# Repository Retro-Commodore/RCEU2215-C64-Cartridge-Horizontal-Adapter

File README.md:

# RCEU2215 - C64 Cartridge Horizontal Adapter
Cartridge vertical to horizontal adapter, i.e. for C128DCR and 1541 Ultimate

This is an adapter I created for my Commodore 128 DCR and 1541 Ultimate 2(+).
I got annoyed that the C128 would reset by cables and the back wall, on the reset switch of any cart with a reset button, due to it's limited space up against the back wall. 
Also the IEC cable connectors would cross tightly and strain the connectors on both IEC and U2 ports. 
The U2+ IEC got moved back in this new design, but not enough, and now the tape connector + audio connectors are in the way.

The result was to make this adapter, and the items below fixes that problem

* 2 (nylon) standoffs 
* 44pin Edge connector 2.54mm pitch, straight

Standoffs and connector can be found on ebay, or perhaps your favorite local store.

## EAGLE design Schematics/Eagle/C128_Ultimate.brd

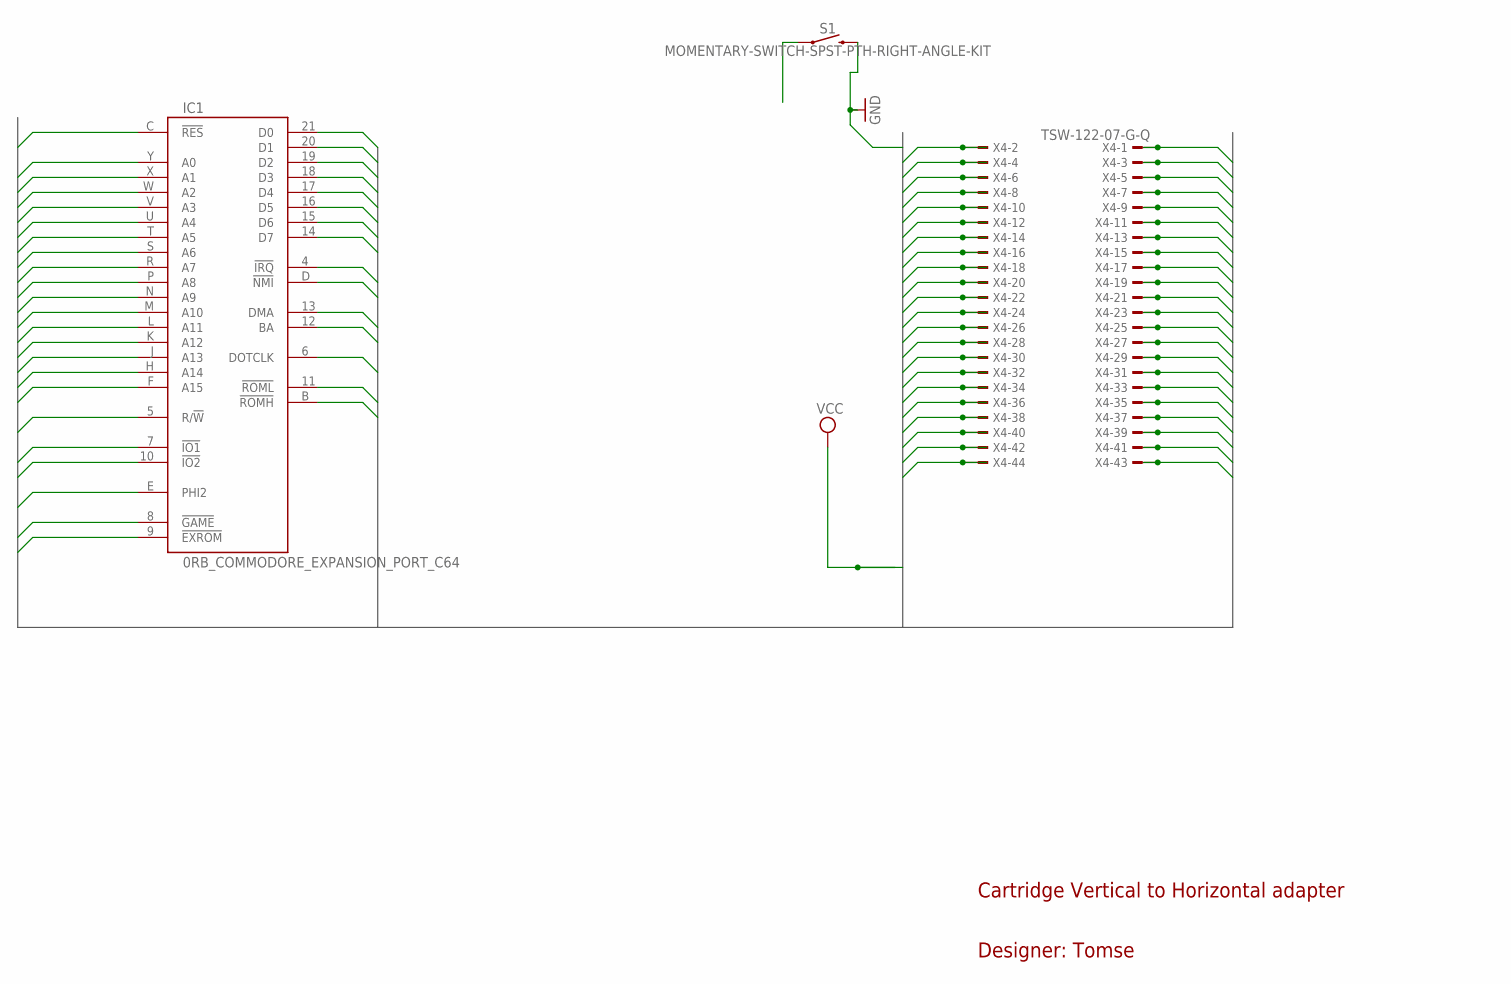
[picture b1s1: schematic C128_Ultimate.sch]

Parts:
IC1: 0RB_COMMODORE_EXPANSION_PORT_C64; 0RB_COMMODORE_MA100-22-2
S1: MOMENTARY-SWITCH-SPST-PTH-RIGHT-ANGLE-KIT; TACTILE_SWITCH_PTH_RIGHT_ANGLE_KIT
X4: TSW-122-07-G-Q; TSW-122-XX-G-Q

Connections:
!DMA: IC1.13 (DMA), X4.26
!EXROM: IC1.9 (!EXROM), X4.18
!GAME: IC1.8 (!GAME), X4.16
!IO1: IC1.7 (!IO1), X4.14
!IO2: IC1.10 (!IO2), X4.20
!IRQ: IC1.4 (!IRQ), X4.8
!NMI: IC1.D (!NMI), X4.7
!RES: IC1.C (!RES), S1.1, X4.5
!ROMH: IC1.B (!ROMH), X4.3
!ROML: IC1.11 (!ROML), X4.22
A0: IC1.Y (A0), X4.41
A1: IC1.X (A1), X4.39
A2: IC1.W (A2), X4.37
A3: IC1.V (A3), X4.35
A4: IC1.U (A4), X4.33
A5: IC1.T (A5), X4.31
A6: IC1.S (A6), X4.29
A7: IC1.R (A7), X4.27
A8: IC1.P (A8), X4.25
A9: IC1.N (A9), X4.23
A10: IC1.M (A10), X4.21
A11: IC1.L (A11), X4.19
A12: IC1.K (A12), X4.17
A13: IC1.J (A13), X4.15
A14: IC1.H (A14), X4.13
A15: IC1.F (A15), X4.11
BA: IC1.12 (BA), X4.24
D0: IC1.21 (D0), X4.42
D1: IC1.20 (D1), X4.40
D2: IC1.19 (D2), X4.38
D3: IC1.18 (D3), X4.36
D4: IC1.17 (D4), X4.34
D5: IC1.16 (D5), X4.32
D6: IC1.15 (D6), X4.30
D7: IC1.14 (D7), X4.28
DOTCLK: IC1.6 (DOTCLK), X4.12
GND: IC1.1 (GND), IC1.22 (GND), IC1.A (GND), IC1.Z (GND), S1.2, X4.1, X4.2, X4.43, X4.44
PHI2: IC1.E (PHI2), X4.9
R!W: IC1.5 (R/!W), X4.10
VCC: IC1.2 (VCC), IC1.3 (VCC), X4.4, X4.6

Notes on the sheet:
Cartridge Vertical to Horizontal adapter
Designer: Tomse

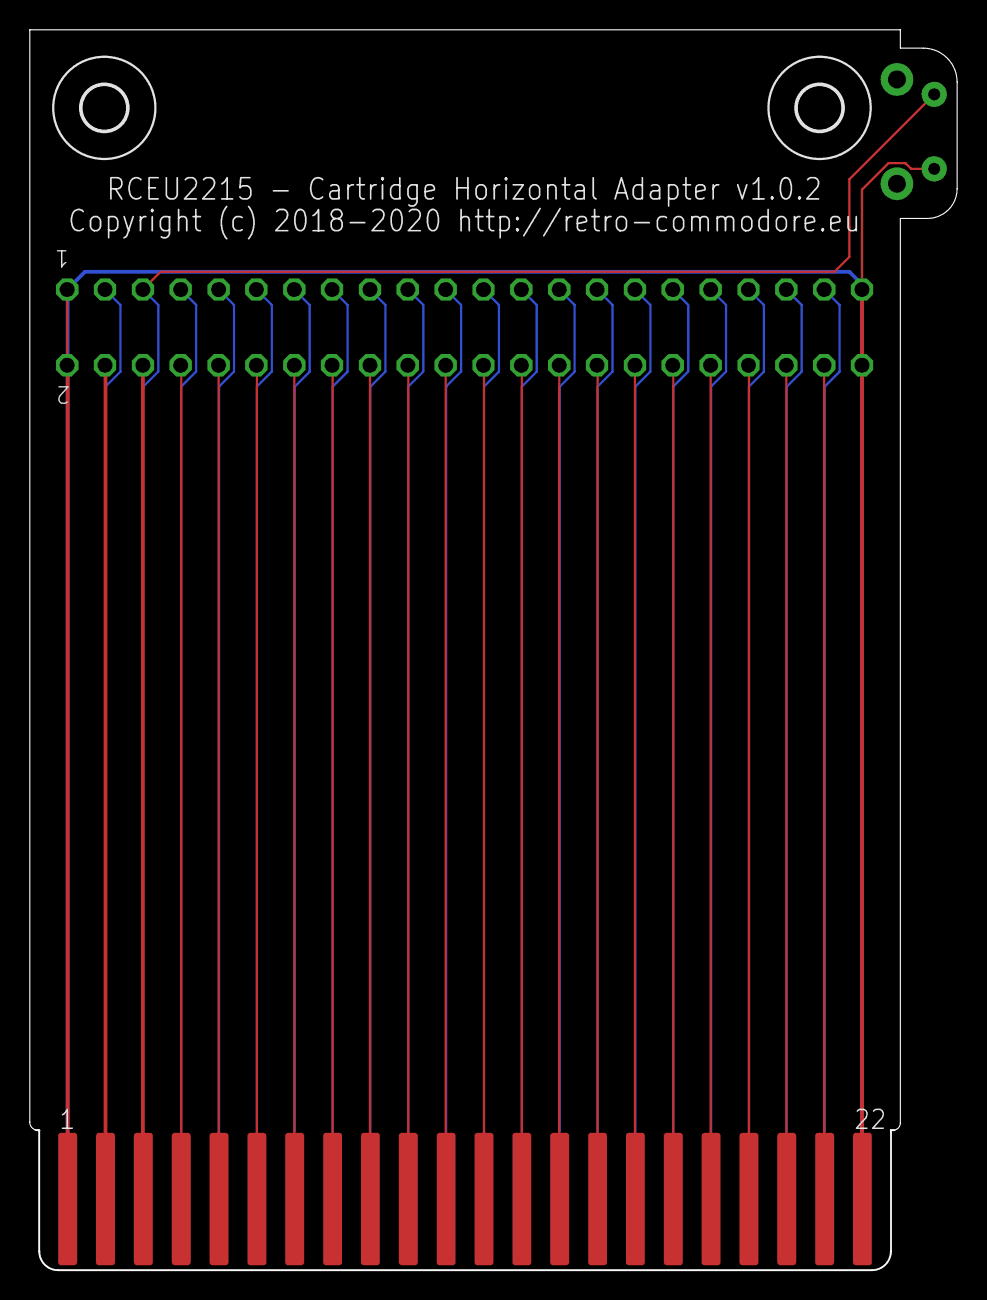
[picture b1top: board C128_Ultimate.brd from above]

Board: 2 copper layers, 62.2 x 83.2 mm, 5 parts (1 on the bottom side), 40 nets.

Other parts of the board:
U$1, U$2: 3,0

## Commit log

2018-10-09 Update Hardware/Pics/Bottom.jpg
    Moved dir to correct location
2018-10-09 Update Hardware/Pics/Top.jpg
    Moved to correct location
2018-10-09 Update Pics/Bottom.jpg
    Moved to correct location
2018-10-09 Update Pics/Top.jpg
    Moved to correct location
2018-10-09 Update Hardware/Eagle/C128_Ultimate.brd
    Properly moved reset button to bottom side
2018-10-09 Update Hardware/Eagle/C128_Ultimate.sch
    Properly moved reset button to bottom side
2018-10-09 Update Hardware/Eagle/C128_Ultimate_2018-10-09_CAM_Files.zip
    Properly moved reset button to bottom side
2018-10-09 Update Hardware/Eagle/C128_Ultimate_2018-01-28_CAM_Files.zip
    removed old cam files - improperly set reset button
2020-04-06 Cosmetic changes

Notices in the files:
Schematics/Eagle/C128_Ultimate.brd:
Copyright (c) 2018-2020 http://retro-commodore.eu
Schematics/Eagle/C128_Ultimate.sch:
DESIGNER: Copyright (c) 2018 http://retro-commodore.eu
parts and their libraries:
SparkFun-Aesthetics: Licensing: Creative Commons ShareAlike 4.0 International - https://creativecommons.org/licenses/by-sa/4.0
